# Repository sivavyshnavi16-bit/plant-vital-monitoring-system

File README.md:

# Plant Vital Monitoring with Industrial Sensors

### Embedded Systems | Teensy 4.0 | SPI/I²C | Sensor Integration | Bluetooth | Data Logging

**Academic Team Project — Technische Universität Chemnitz, Germany | July 2025**

## Project Overview

This project explores a non-invasive plant monitoring system using industrial-grade inductive and capacitive sensing technologies.

The prototype combines the **LDC1101 inductance-to-digital converter** and **FDC2214 capacitance-to-digital converter** with a **Teensy 4.0 microcontroller**.

The system was designed to acquire sensor measurements, record timestamps, store data locally, and transmit readings wirelessly for remote monitoring.

## Project Objectives

- Develop an embedded platform for non-invasive plant monitoring.
- Interface industrial sensors using SPI and I²C.
- Integrate real-time timestamps using an RTC module.
- Implement local data logging using an SD card.
- Enable wireless monitoring through Bluetooth.
- Investigate hardware communication problems using debugging tools.

## Hardware Components

| Component | Function |
|---|---|
| Teensy 4.0 | Main microcontroller |
| LDC1101 | Inductive sensing |
| FDC2214 | Capacitive sensing |
| HW-689 RTC | Measurement timestamps |
| MicroSD Card Adapter | Local data logging |
| Bluetooth Module | Wireless data transmission |
| Custom PCBs | Sensor circuit integration |

## Technologies Used

**Programming:** Embedded C/C++, Arduino/Teensy environment

**Communication:** SPI, I²C, UART, Bluetooth

**Hardware Design:** Autodesk EAGLE, PCB layout, circuit assembly

**Debugging:** Logic analyzer, multimeter, serial monitoring

**Libraries:** SPI, Wire, SdFat, RTClib

## System Architecture

The Teensy 4.0 acts as the central controller.

- **LDC1101:** SPI-based inductive sensing.
- **FDC2214:** I²C-based capacitive sensing.
- **RTC:** Timestamp generation.
- **SD Card:** Local storage of measurements.
- **Bluetooth:** Wireless transmission to a mobile device.
- **USB Serial:** Monitoring and debugging through a computer.

## Firmware Development

The project includes embedded firmware for:

- LDC1101 register configuration and sensor data acquisition.
- FDC2214 register configuration and I²C communication.
- RTC initialization and timestamp retrieval.
- SD card initialization, file writing, and reading.
- Bluetooth-based transmission of sensor measurements.

The firmware was developed for the Teensy 4.0 using C/C++.

## Testing and Results

The prototype successfully demonstrated:

- Real-time LDC1101 sensor data acquisition using SPI.
- RTC-based timestamp generation.
- SD card read/write operations.
- Wireless transmission of sensor data to a mobile application.
- Serial monitoring of measurements on a computer.

### Hardware Debugging

During FDC2214 integration, an I²C communication problem was investigated using a logic analyzer.

A missing acknowledgment (ACK) was observed, and the investigation identified incorrect PCB connections. The team corrected the design and prepared an updated PCB layout.

This debugging process demonstrated the importance of hardware-software verification and systematic troubleshooting.

## My Contributions

My primary responsibilities included:

- Bluetooth communication configuration.
- Real-Time Clock (RTC) integration.
- SD card configuration and data logging.
- Supporting system integration and testing.

I also gained experience with the overall sensor architecture, embedded firmware, PCB design process, and hardware debugging through this collaborative project.

## Project Team

This project was completed as part of the Embedded Systems Project Lab at Technische Universität Chemnitz.

**Team members:**

- Komma Siva Vyshnavi Reddy
- Sheikh Zeeshan Ahmed
- Rushikesh Lakadkar
- Randhir Bhagat

## Future Improvements

Potential future enhancements include:

- Further validation of FDC2214 measurements.
- Improved sensor calibration and measurement analysis.
- A dedicated dashboard for monitoring plant conditions.
- Long-term data visualization and trend analysis.
- More compact hardware integration.

## Contact

**Vyshnavi Reddy**

Embedded Systems Engineer | Firmware & Electronics

Email: sivavyshnavi16@gmail.com

LinkedIn: https://www.linkedin.com/in/vyshnavi-reddy-344b66211

*Academic engineering project focused on embedded sensing, firmware integration, wireless communication, and hardware validation.*

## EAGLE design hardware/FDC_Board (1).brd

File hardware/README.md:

Autodesk EAGLE schematics and PCB layouts for the LDC1101 and FDC2214 sensor circuits used in the Plant Vital Monitoring project.

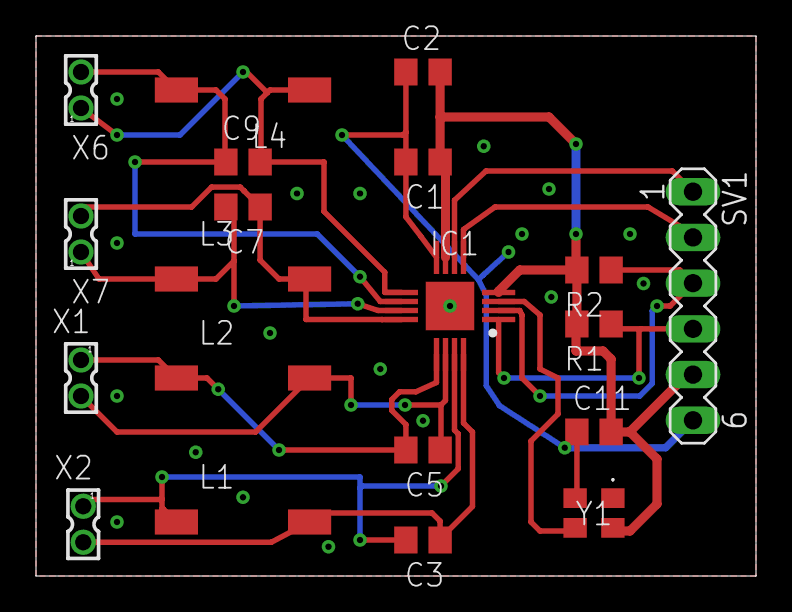
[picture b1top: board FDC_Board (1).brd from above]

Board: 2 copper layers, 40.0 x 30.0 mm, 20 parts (0 on the bottom side), 15 nets.

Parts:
C1, C2, C3, C5, C7, C9, C11: C0805
IC1: FDC2214RGHR; QFN50P400X400X80-17N
L1, L2, L3, L4: L8530M
R1, R2: R0805
SV1: MA06-1
X1, X2, X6, X7: 332-02
Y1: ASE-40.000MHZ-E-T; ASE40000MHZET

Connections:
GND: C1.2, C2.1, C11.1, IC1.8, IC1.17, SV1.6, Y1.2
unnamed: C3.2, IC1.15, L1.1, X2.1
unnamed: IC1.1, R1.1, SV1.4
unnamed: IC1.6, SV1.1
unnamed: IC1.5, SV1.2
unnamed: C5.2, IC1.13, L2.1, X1.1
unnamed: C7.1, IC1.12, L3.2, X7.2
unnamed: C5.1, IC1.14, L2.2, X1.2
unnamed: IC1.3, Y1.3
unnamed: IC1.2, R2.1, SV1.3
unnamed: C7.2, IC1.11, L3.1, X7.1
unnamed: C3.1, IC1.16, L1.2, X2.2
unnamed: C9.2, IC1.9, L4.1, X6.1
unnamed: C9.1, IC1.10, L4.2, X6.2
VCC: C1.1, C2.2, C11.2, IC1.4, IC1.7, R1.2, R2.2, SV1.5, Y1.4

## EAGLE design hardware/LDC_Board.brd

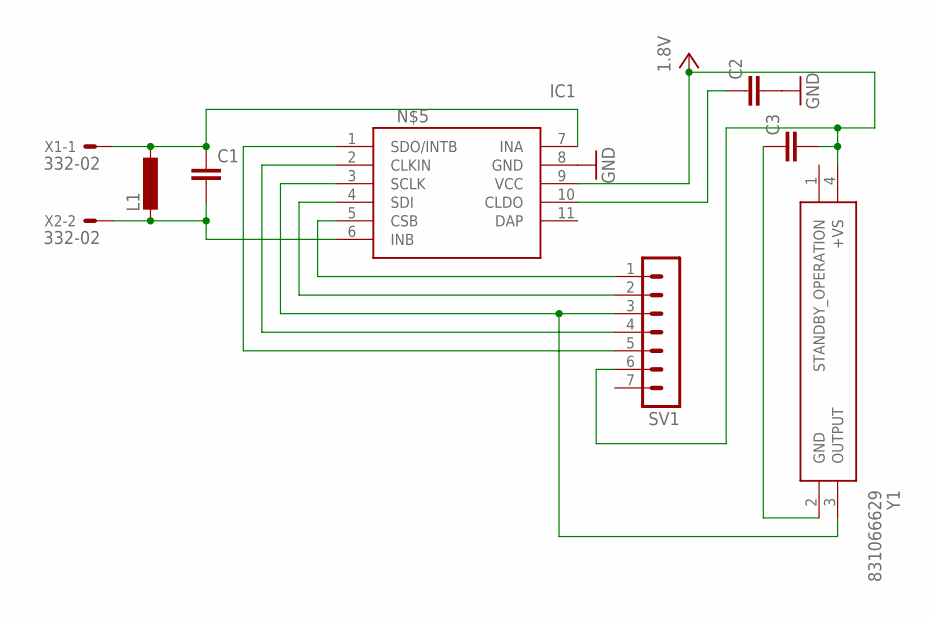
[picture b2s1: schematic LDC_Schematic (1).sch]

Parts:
C1, C2, C3: C-EUC0805; C0805
IC1: LDC1101DRCR; TPS74901DRCR
L1: L-EUL8530M; L8530M
SV1: MA07-1
X1, X2: 332-02
Y1: 831066629

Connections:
GND: C2.2, IC1.8 (GND)
unnamed: C1.2, IC1.6 (INB), L1.2, X2.2
unnamed: C1.1, IC1.7 (INA), L1.1, X1.1
unnamed: C3.1, Y1.2 (GND)
unnamed: C2.1, IC1.10 (CLDO)
unnamed: IC1.1 (SDO/INTB), SV1.5
unnamed: IC1.2 (CLKIN), SV1.4
unnamed: IC1.4 (SDI), SV1.2
unnamed: IC1.5 (CSB), SV1.1
unnamed: IC1.3 (SCLK), SV1.3, Y1.3 (OUTPUT)
VCC: C3.2, IC1.9 (VCC), SV1.6, Y1.4 (+VS)

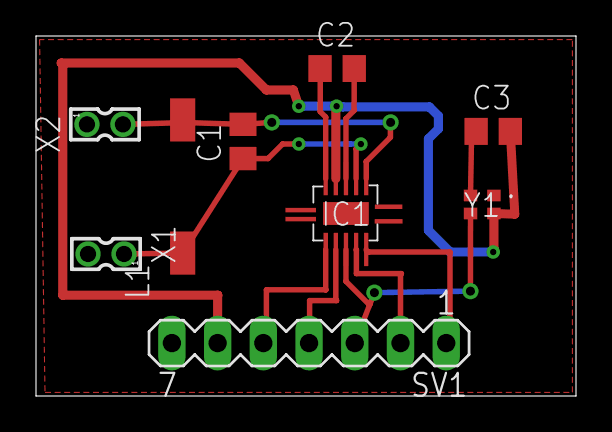
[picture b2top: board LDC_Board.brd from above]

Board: 2 copper layers, 30.0 x 20.0 mm, 9 parts (0 on the bottom side), 11 nets.
